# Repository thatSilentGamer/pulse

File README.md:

# Custom ESP32-S3 Spotify Controller Macro-Pad

A hardware macro-pad designed from scratch to provide physical control over Spotify and computer audio. This project features mechanical keyswitches, a rotary encoder for volume tracking, and an integrated display for media status.

---

## Project Overview

### What It Is
This is a compact hardware macro-pad designed as a **Spotify Controller**. It features two **Cherry MX2A Speed Silver switches** for skipping tracks or pausing music, an **EC11 rotary encoder** for volume scrolling, and a **TENSTAR ROBOT 1x9 Pin SPI Display** tilted at an angle to show track info.

### Why I Made It
I engineered this controller to bridge digital media apps with hardware. The goal was to build a dedicated desktop tool that lets me control music instantly without switching windows.

### How It Works
* **Media Switches:** The Cherry MX2A Speed Silvers are soldered directly to a custom PCB, passing through a top case layer for stability.
* **Volume Encoder:** Provides a rotating dial interface to control system volume or track scrolling, and it has an integrated click-switch.
* **Display Output:** The sequential 1x9 pin header channels hardware SPI communication straight from the ESP32-S3 Mini, enabling graphics for media feedback.
* **Power & Control:** Fully powered and controlled via a USB-C connection driven by the ESP32-S3 Mini processor.

---

## Project Gallery

---

## Mechanical & CAD Design

**[Click here to view the Onshape 3D CAD Assembly & Source Files](https://cad.onshape.com/documents/9e875fa0eb3d29beb0a7e423/w/634ce2adc409bcbb121e172c/e/cf97eb71c9d871e1e5143c14)**

The case is a two-part shell (top piece and bottom base) that is secured together using **M2/M3 mechanical screws through internal mounting standoffs** that align with the PCB's mounting holes (H1–H4). This ensures a rigid, durable enclosure that holds the electronics firmly in place without relying on friction, tape, or glue.

* **Material Clearances:** The switch holes are slightly larger than they need to be so that they don't get stuck if the 3D print shrinks or over-extrudes a bit.
* **Flush Screen Housing:** The angled part for the screen meets the flat top completely flush so there isn't a weird lip sticking out.
* **Vertical Component Stack:** The case is deep enough so the pins on the bottom of the PCB don't hit the bottom of the shell.

---

## Build Guide & Instructions

### 1. Bill of Materials (BOM)
| Item Name | Size / Specs | Quantity | Cost (Each) | Total Cost | Purchase Link |
| :--- | :--- | :---: | :---: | :---: | :--- |
| ESP32 | 38pin type c | 1 | $8.80 | $8.80 | [AliExpress Link](https://www.aliexpress.us/item/3256804511368849.html) |
| Cherry MX2A Speed Silver 45g Linear Switch | PCB RGB LED | 2 | $0.40 | $0.80 | [Mechanical Keyboards Link](https://mechanicalkeyboards.com/products/cherry-mx2a-speed-silver-45g-linear?variant=48015859876140) |
| EC11 w/ Push Button (rotary encoder) | 20mm Plum handle | 1 | $0.96 | $0.96 | [AliExpress Link](https://www.aliexpress.us/item/3256806507128635.html) |
| Encoder Knob | O 20x13mm | 1 | $0.99 | $0.99 | [AliExpress Link](https://www.aliexpress.us/item/3256808286803013.html) |
| TFT Display | 3.5 inch | 1 | $0.99 | $0.99 | [AliExpress Link](https://www.aliexpress.us/item/3256805988905985.html) |
| WS2812 LED Light strip | 1m | 1 | $0.99 | $0.99 | [AliExpress Link](https://www.aliexpress.us/item/3256806235758108.html) |
| Shine-through keycaps | Black-97 | 1 | $8.35 | $8.35 | [AliExpress Link](https://www.aliexpress.us/item/3256808975886837.html) |
| USB-C Cable | 100W Black | 1 | $5.28 | $5.28 | [AliExpress Link](https://www.aliexpress.us/item/2255800615813072.html) |
| 22AWG Electric Wire | 25m | 1 | $0.99 | $0.99 | [AliExpress Link](https://www.aliexpress.us/item/3256807019779669.html) |
| Resistor Set | 300pcs in box | 1 | $3.37 | $3.37 | [AliExpress Link](https://www.aliexpress.us/item/3256807120498276.html) |
| Capacitor Set | n/a | 1 | $2.05 | $2.05 | [AliExpress Link](https://www.aliexpress.com/item/3256806914843833.html) |
| Electrolytic Capacitor | 10V1000UF 20PCS | 1 | $0.99 | $0.99 | [AliExpress Link](https://www.aliexpress.us/item/3256810280290722.html) |
| Brass Heatset inserts | M2, M2.5, M3 (500PCS) | 1 | $1.59 | $1.59 | [AliExpress Link](https://www.aliexpress.us/item/3256805603102147.html) |
| M2 Screws | 482pcs M2 | 1 | $0.99 | $0.99 | [AliExpress Link](https://www.aliexpress.us/item/3256806973435795.html) |
| M3 Screws | 392pcs M3 | 1 | $0.99 | $0.99 | [AliExpress Link](https://www.aliexpress.us/item/3256806973435795.html) |
| 3D Printing | n/a | 1 | $10.00 | $10.00 | n/a |
| SK6812 MINI-E RGB lights | 100PCS | 1 | $0.99 | $0.99 | [AliExpress Link](https://www.aliexpress.us/item/3256805007401420.html) |
| | | | **Total Cost:** | **$48.72** | |

### 2. PCB & Wiring Layout
* The project utilizes a custom printed circuit board designed in KiCad (source files located in `/Electronics`). 
* **Switches:** Solder the Cherry MX2A Speed Silver switches into the footprint designated on the top side of the board.
* **Encoder:** Mount and solder the EC11 rotary encoder into position `SW1`.
* **Display:** Connect the 1x9 Pin SPI Display header directly to `J1`, which routes hardware SPI pins from the ESP32-S3 WROOM module.
* **Mounting:** Use M2/M3 mechanical screws through standoffs `H1`–`H4` to secure the soldered PCB firmly inside the 3D-printed bottom shell.

### 3. Firmware & Flashing Instructions
1. Download and install the Arduino IDE along with the ESP32 board definitions and required libraries (`TFT_eSPI`, `BleKeyboard`, `ESP32Encoder`, and `FastLED`).
2. Open `/Firmware/pulse.ino` in your IDE.
3. Connect the ESP32-S3 to your computer via USB-C.
4. Select **ESP32S3 Dev Module** as your target board and select the correct COM port.
5. Click **Upload** to compile and flash the firmware onto the microcontroller.

### 4. Usage Guide
Once flashed and powered via USB-C, Pulse will boot up and display *"Pulse is online."* on the screen while lighting up the green underglow.
* **Pairing:** Open your computer or phone's Bluetooth settings and pair with the device named **"Pulse Controller"**.
* **Volume Control:** Turn the rotary encoder knob clockwise to increase system volume, and counter-clockwise to decrease volume.
* **Play/Pause:** Press down on the rotary encoder knob (integrated click switch) to toggle media play/pause.
* **Track Navigation:** Press the left Cherry MX switch (`BTN_SKIP_BCK`) to jump to the previous track, or the right switch (`BTN_SKIP_FWD`) to skip to the next track on Spotify!

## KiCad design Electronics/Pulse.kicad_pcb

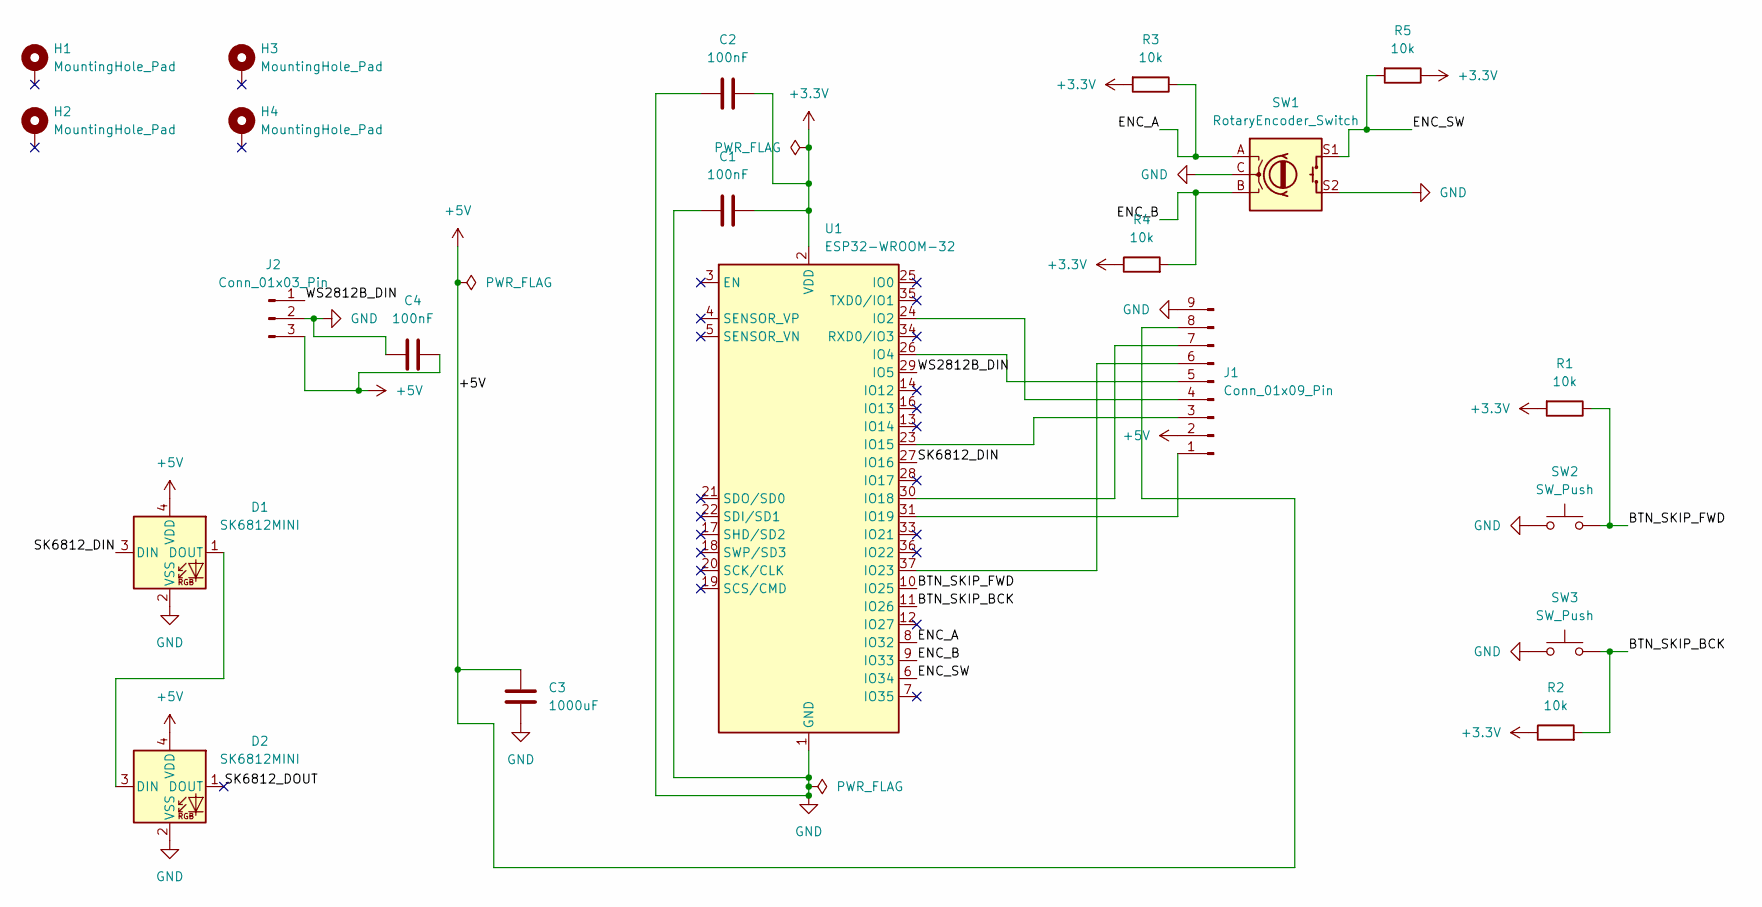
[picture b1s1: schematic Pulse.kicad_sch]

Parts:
C1, C2, C4: 100nF; C_Disc_D5.0mm_W2.5mm_P5.00mm
C3: 1000uF; C_Radial_D8.0mm_H11.5mm_P3.50mm
D1, D2: SK6812MINI; MX_SK6812MINI-E_REV
H1, H2, H3, H4: MountingHole_Pad; MountingHole_2.2mm_M2_Pad_Via
J1: Conn_01x09_Pin; PinHeader_1x09_P2.54mm_Vertical
J2: Conn_01x03_Pin; PinHeader_1x03_P2.54mm_Vertical
R1, R2, R3, R4, R5: 10k; R_Axial_DIN0207_L6.3mm_D2.5mm_P10.16mm_Horizontal
SW1: RotaryEncoder_Switch; RotaryEncoder_Alps_EC11E-Switch_Vertical_H20mm_CircularMoun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
SW2, SW3: SW_Push; SW_Cherry_MX1A_1.00u_PCB
U1: ESP32-WROOM-32; ESP32-DevKitC

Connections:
+3.3V: C1.2, C2.2, R1.2, R2.1, R3.2, R4.1, R5.1, U1.2 (VDD)
+5V: C3.2, C4.2, D1.4 (VDD), D2.4 (VDD), J1.2, J1.8, J2.3
/BTN_SKIP_BCK: R2.2, SW3.2, U1.11 (IO26)
/BTN_SKIP_FWD: R1.1, SW2.2, U1.10 (IO25)
/ENC_A: R3.1, SW1.A, U1.8 (IO32)
/ENC_B: R4.2, SW1.B, U1.9 (IO33)
/ENC_SW: R5.2, SW1.S1, U1.6 (IO34)
/SK6812_DIN: D1.3 (DIN), U1.27 (IO16)
/SK6812_DOUT: D2.1 (DOUT)
/WS2812B_DIN: J2.1, U1.29 (IO5)
GND: C1.1, C2.1, C3.1, C4.1, D1.2 (VSS), D2.2 (VSS), J1.9, J2.2, SW1.C, SW1.S2, SW2.1, SW3.1, U1.1 (GND)
unnamed: D1.1 (DOUT), D2.3 (DIN)
unnamed: J1.1, U1.31 (IO19)
unnamed: J1.3, U1.23 (IO15)
unnamed: J1.4, U1.24 (IO2)
unnamed: J1.5, U1.26 (IO4)
unnamed: J1.6, U1.37 (IO23)
unnamed: J1.7, U1.30 (IO18)

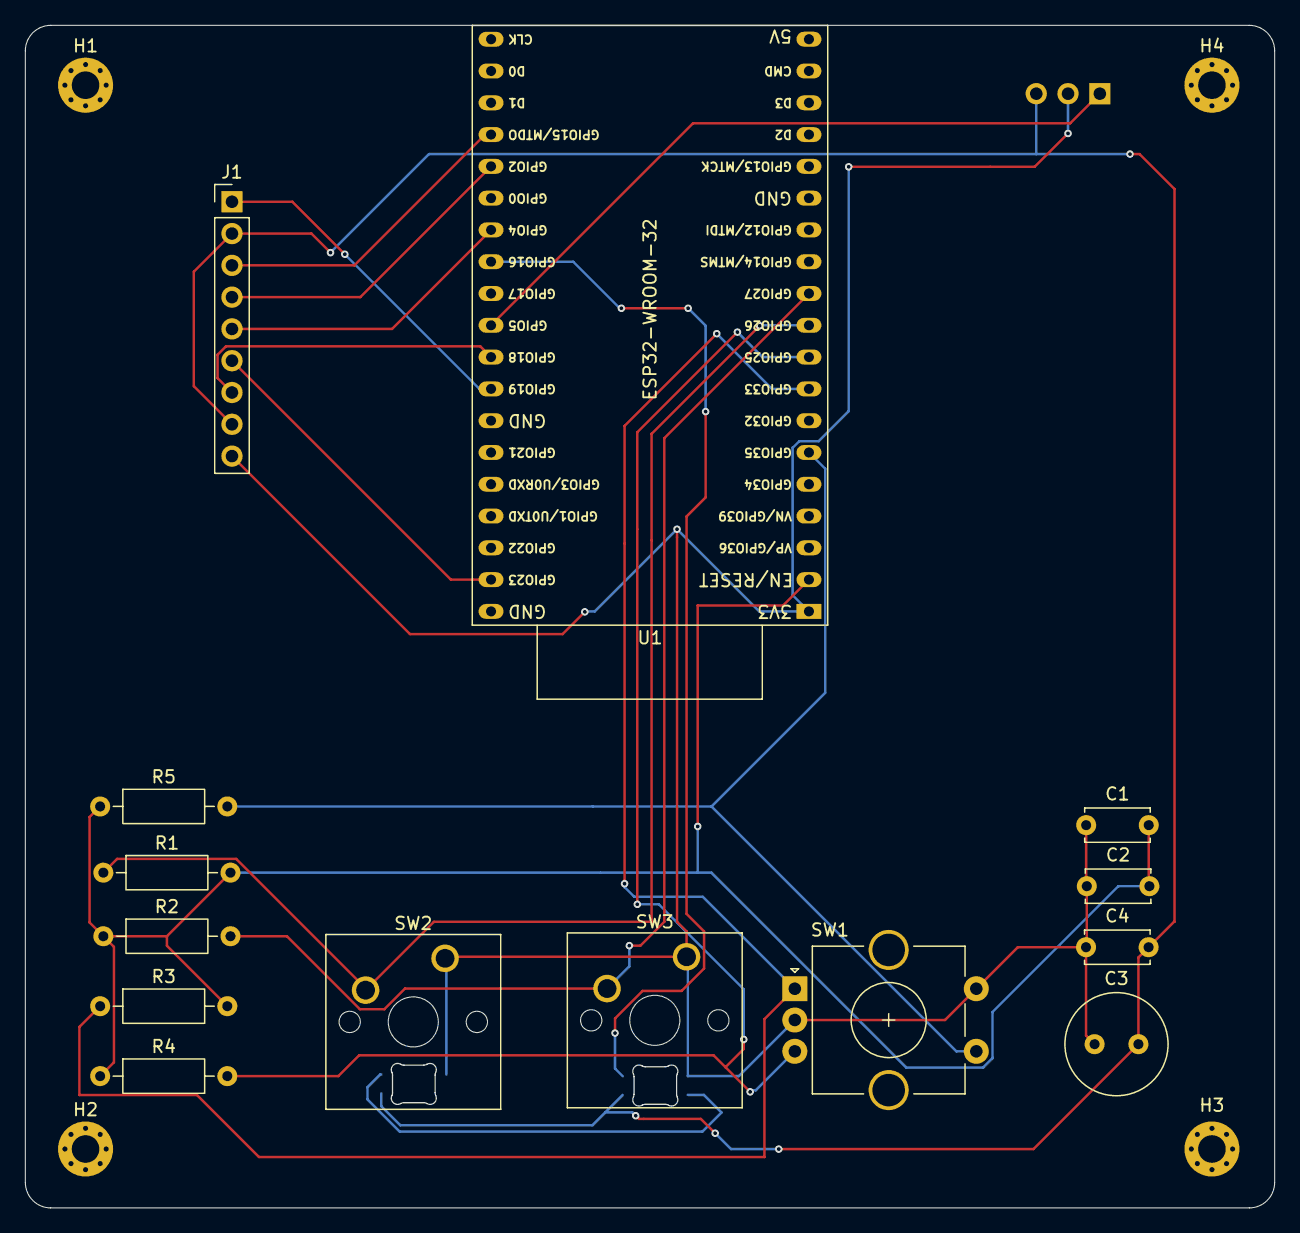
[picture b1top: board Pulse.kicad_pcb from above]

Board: 2 copper layers, 99.8 x 94.4 mm, 21 parts (1 on the bottom side), 17 nets.

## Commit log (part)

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2026-06-26 Update README with project overview and design details
    Added detailed project description and specifications for the Custom ESP32-S3 Spotify Controller Macro-Pad.
2026-06-26 Update project description in README.md
    Removed the word 'original' from project description.
2026-06-26 Update BOM.csv with total cost and item links
    Added total cost summary and updated item links.
2026-06-26 Update BOM.csv format and link syntax
2026-06-26 Fix formatting and links in BOM.csv
    Updated BOM.csv to correct formatting and links.
2026-06-26 Update BOM.csv with corrected links and formatting
2026-06-26 Revise BOM with new links and updated costs
    Updated product links and prices in BOM.csv.
2026-06-26 Update BOM.csv with new items and costs
2026-06-26 Update BOM.csv with new item entries
2026-06-26 Create onshape-link
